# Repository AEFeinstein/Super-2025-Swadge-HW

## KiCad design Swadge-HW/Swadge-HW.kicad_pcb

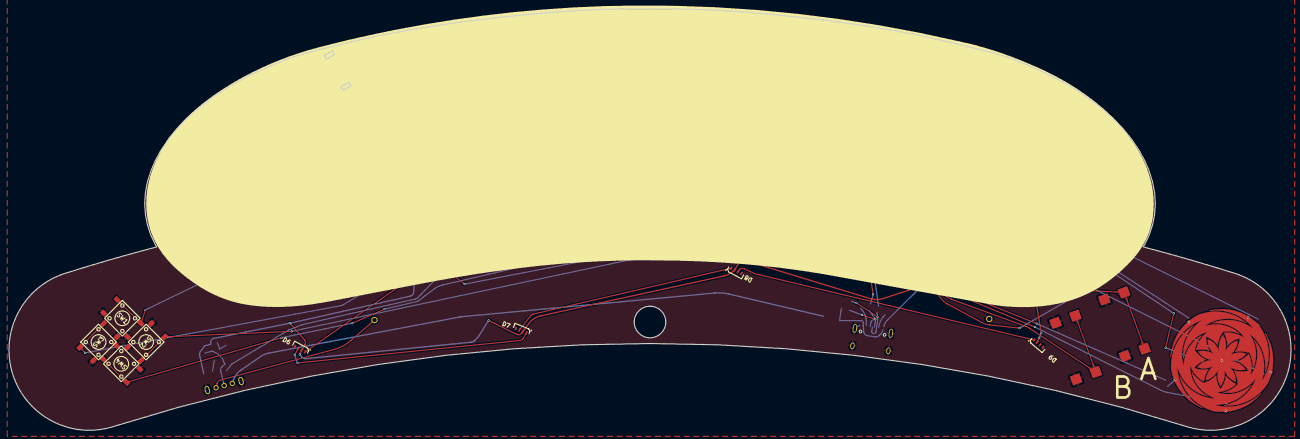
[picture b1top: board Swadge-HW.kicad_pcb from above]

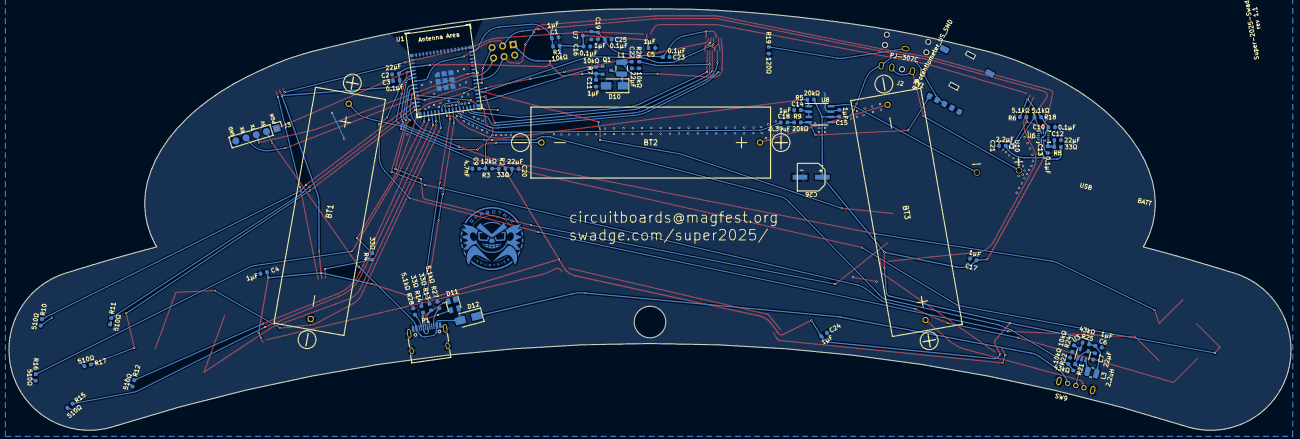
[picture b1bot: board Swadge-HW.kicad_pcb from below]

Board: 2 copper layers, 305.0 x 100.2 mm, 96 parts (71 on the bottom side), 76 nets.

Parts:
BT1, BT2, BT3: Battery; 2460
C1, C4, C5, C6, C11, C14, C15, C17, C19, C24: 1μF; C_0603_1608Metric
C2, C7, C12, C20, C22: 22μF; C_0603_1608Metric
C3, C10, C13, C16, C23, C25: 0.1μF; C_0603_1608Metric
C9: 4.7nF; C_0603_1608Metric
C18: 0.39uF; C_0603_1608Metric
C21: 2.2μF; C_0603_1608Metric
C26: 470μF; C_Radial_D6.3_L5.8_P5.34
D1, D2, D3, D4, D5, D6, D7, D8, D9: LC8812B-4020; 4020PAD
D10, D12: D; D_SMA
D11: SP0503BAHT; SOT-143
J1: SAO; PinSocket_2x03_P2.54mm_Vertical
J2: PJ-307C
J3: PGM; PinHeader_1x05_P2.54mm_Vertical
L1: 33uH_500mA; L_1210_3225Metric
L3: 2.2uH; L_1008_2520Metric
MK1: Microphone; INGHAi_MIC_GMI4013S-2C58DB
N1: Board Outline; longdog-outline
N2: Condiment Acrylic; longdog-condiment
P1: USB_C_Plug_USB2.0; USB_C_Receptacle_HRO_TYPE-C-31-M-12
Q1: Q_PMOS_GSD; SOT-23
R1, R7, R22, R24, R26: 10kΩ; R_0603_1608Metric
R2, R4, R8, R13, R14: 33Ω; R_0603_1608Metric
R3: 12kΩ; R_0603_1608Metric
R5, R9: 20kΩ; R_0603_1608Metric
R6, R18, R27, R28: 5.1kΩ; R_0603_1608Metric
R10, R11, R12, R15, R16, R17: 510Ω; R_0603_1608Metric
R19: 120Ω; R_0603_1608Metric
R21, R25: 43kΩ; R_0603_1608Metric
RV1: R_Potentiometer_US_SMD; RK10J11R001Y
SW1, SW2, SW3, SW4, SW5, SW6: YTS-D003-1A
SW7, SW8: B3FS-4002P; B3FS4002P
SW9: SW_SPDT_1825232-1; 1825232-1
U1: ESP32-S2-MINI-1
U2: RB017A1505A; NULL
U3: MT3410; SOT-23-5
U4: Touch_Teeth_5b
U5: RB017A1505A_Connector; HCTL HC-FPC-03-10-15RLTAG
U6: LSM6DSL; LGA-14_3x2.5mm_P0.5mm_LayoutBorder3x4y
U7: GENERIC_LDO_2.8; SOT-23
U8: FM8002A; SOP-8_3.9x4.9mm_P1.27mm
U9: INGHAi_GSPK2307P-8R1W; INGHAi GSPK2308P-8R0.5W
U10: BGA-4-.83x.83

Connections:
5VIN: D11.4 (K), D12.2 (A), J3.2, P1.A4_B9 (VBUS), P1.A9_B4 (VBUS)
+3V3: C2.1, C3.1, C4.1, C5.1, C6.1, C10.1, C11.1, C15.1, C16.1, C17.1, C21.1, C24.1, C26.1, D1.2 (VDD), D2.2 (VDD), D3.2 (VDD), D4.2 (VDD), D5.2 (VDD), D6.2 (VDD), D7.2 (VDD), D8.2 (VDD), D9.2 (VDD), J1.1, L3.1, Q1.2 (S), R1.1, R2.2, R5.1, R6.2, R7.1, R8.2, R18.1, R25.2, U1.3 (3V3), U6.5 (VDDIO), U6.12 (CS), U7.3 (IN), U8.6 (VDD), U10.B1 (VDD)
+5V: D12.1 (K), SW9.1 (A)
BATTMID: BT1.1 (+), BT2.2 (-)
BATTMID2: BT2.1 (+), BT3.2 (-)
BATTPLUS: BT3.1 (+), SW9.3 (C)
BTN_1: J3.1, SW1.1, SW1.2, U1.4 (GPIO0/BOOT)
BTN_2: SW2.1, SW2.2, U1.5 (GPIO1/ADC1_CH0)
BTN_3: SW3.1, SW3.2, U1.6 (GPIO2/ADC1_CH1)
BTN_4: SW4.1, SW4.2, U1.8 (GPIO4/ADC1_CH3)
BTN_5: SW5.1, SW5.2, U1.9 (GPIO5/ADC1_CH4)
BTN_6: SW6.1, SW6.2, U1.12 (GPIO8/ADC1_CH7)
BTN_7: SW7.1 (COM_1), SW7.2 (COM_2), U1.19 (GPIO15/ADC2_CH4/XTAL_32K_P)
BTN_8: SW8.1 (COM_1), SW8.2 (COM_2), U1.20 (GPIO16/ADC2_CH5/XTAL_32K_N)
CC1: P1.A5 (CC1), R28.2
CC2: P1.B5 (CC2), R27.2
EN: C1.1, R1.2, U1.45 (CHIP/PU/RESET)
GND: BT1.2 (-), C1.2, C2.2, C3.2, C4.2, C5.2, C6.2, C7.2, C9.1, C10.2, C11.2, C12.2, C13.2, C14.1, C15.2, C16.2, C17.2, C19.2, C20.2, C21.2, C22.2, C23.2, C24.2, C25.2, C26.2, D1.4 (GND), D2.4 (GND), D3.4 (GND), D4.4 (GND), D5.4 (GND), D6.4 (GND), D7.4 (GND), D8.4 (GND), D9.4 (GND), D10.2 (A), D11.1 (A), J1.2, J3.5, MK1.1 (-), P1.A1_B12 (GND), P1.A12_B1 (GND), P1.S1 (SHIELD), R19.1, R22.2, R24.1, R26.2, R27.1, R28.1, SW1.3, SW1.4, SW2.3, SW2.4, SW3.3, SW3.4, SW4.3, SW4.4, SW5.3, SW5.4, SW6.3, SW6.4, SW7.3 (NO_1), SW7.4 (NO_2), SW8.3 (NO_1), SW8.4 (NO_2), SW9.4 (D), SW9.5 (E), U1.1 (GND), U1.2 (GND), U1.30 (GND), U1.42 (GND), U1.43 (GND), U1.46 (GND), U1.47 (GND), U1.48 (GND), U1.49 (GND), U1.50 (GND), U1.51 (GND), U1.52 (GND), U1.53 (GND), U1.54 (GND), U1.55 (GND), U1.56 (GND), U1.57 (GND), U1.58 (GND), U1.59 (GND), U1.60 (GND), U1.61 (GND), U1.62 (GND), U1.63 (GND), U1.64 (GND), U1.65 (GND), U3.2 (GND), U5.1 (GND), U5.6 (GND), U5.9 (GND), U5.12 (LED-), U5.13 (LED-), U5.16 (GND), U5.17 (GND), U6.1 (SA0), U6.2 (SDx), U6.3 (SCx), U6.6 (GND), U6.7 (GND), U7.1 (GND), U8.7 (GND), U10.A1 (VSS)
GPIO40: J1.5, U1.36 (MTDO/JTAG/GPIO40)
GPIO42: J1.6, U1.38 (MTMS/JTAG/GPIO42)
LCD28: C19.1, C23.1, C25.1, U5.2 (VCC1.8V), U5.10 (VDD2.8V), U7.2 (OUT)
LED: R4.2, U1.35 (MTCK/JTAG/GPIO39)
MIC: C9.2, MK1.2 (+), R3.2, U1.11 (GPIO7/ADC1_CH6)
unnamed: C18.1, R9.1
unnamed: C20.1, R2.1, R3.1
unnamed: D1.1 (IN), R4.1
unnamed: D1.3 (OUT), D2.1 (IN)
unnamed: D2.3 (OUT), D3.1 (IN)
unnamed: D3.3 (OUT), D4.1 (IN)
unnamed: D4.3 (OUT), D5.1 (IN)
unnamed: D5.3 (OUT), D6.1 (IN)
unnamed: D6.3 (OUT), D7.1 (IN)
unnamed: D7.3 (OUT), D8.1 (IN)
unnamed: D8.3 (OUT), D9.1 (IN)
unnamed: D10.1 (K), L1.1, Q1.3 (D)
unnamed: J2.1, R19.2
unnamed: D11.2 (K), P1.A7 (DN1), P1.B7 (DN2), R14.2
unnamed: D11.3 (K), P1.A6 (DP1), P1.B6 (DP2), R13.2
unnamed: R24.2, R25.1, U3.5 (FB)
unnamed: L3.2, U3.3 (LX)
unnamed: R10.2, U4.1 (Bottom)
unnamed: R17.2, U4.6 (Center)
unnamed: R16.2, U4.5 (Left)
unnamed: R11.2, U4.2 (Right)
unnamed: R15.2, U4.4 (Top_Left)
unnamed: R12.2, U4.3 (Top_Right)
unnamed: C12.1, C13.1, R8.1, U6.8 (VDD)
unnamed: C14.2, U8.2 (Bypass), U8.3 (IN+)
unnamed: R9.2, RV1.1, U8.4 (IN-)
unnamed: J2.2, J2.5, RV1.2, U8.5 (VO1)
unnamed: U8.8 (VO2), U9.2 (-)
unnamed: J2.3, J2.4, U9.1 (+)
RX: J3.4, U1.40 (GPIO44/U0RXD/PROG)
SCL: J1.4, R6.1, U1.37 (MTDI/JTAG/GPIO41), U6.13 (SCL), U10.A2 (SCL)
SDA: J1.3, R18.2, U1.7 (GPIO3/ADC1_CH2), U6.14 (SDA), U10.B2 (SDA)
SNODE: C7.1, R21.2, SW9.2 (B), U3.1 (EN), U3.4 (VIN)
SPK: C18.2, U1.21 (ADC2_CH7/DAC_2/GPIO17)
SPK_SHDN: R5.2, U1.22 (ADC2_CH6/DAC_1/GPIO18), U8.1 (Shutdown)
TFTATP: Q1.1 (G), R7.2, U1.31 (GPIO35)
TFT_CS: U1.29 (GPIO34), U5.3 (CS)
TFT_FMARK: U1.28 (GPIO33), U5.11 (FMARK)
TFT_LEDA: C22.1, L1.2, U5.14 (LED+), U5.15 (LED+)
TFT_RESET: U1.34 (GPIO38), U5.4 (RESET)
TFT_RS: R26.1, U1.25 (GPIO21), U5.5 (RS)
TFT_SCL: U1.32 (GPIO36), U5.7 (SCL)
TFT_SDA: U1.33 (GPIO37), U5.8 (SDA)
TOUCH_1: R10.1, U1.13 (GPIO9/ADC1_CH8)
TOUCH_2: R11.1, U1.14 (GPIO10/ADC1_CH9)
TOUCH_3: R17.1, U1.15 (GPIO11/ADC2_CH0)
TOUCH_4: R16.1, U1.16 (GPIO12/ADC2_CH1)
TOUCH_5: R12.1, U1.17 (GPIO13/ADC2_CH2)
TOUCH_6: R15.1, U1.18 (GPIO14/ADC2_CH3)
TX: J3.3, U1.39 (GPIO43/U0TXD/PROG)
USB_D+: R13.1, U1.24 (USB_D+/ADC2_CH9/GPIO20)
USB_D-: R14.1, U1.23 (USB_D-/ADC2_CH8/GPIO19)
VMON: R21.1, R22.1, U1.10 (GPIO6/ADC1_CH5)

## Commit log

2024-10-06 Add longdog footprint
    longdog
2024-11-15 longdog
    new outline and silk for longdog variant
2024-11-15 longdog
    longdog layout
2024-11-15 art adjustment
2024-11-18 shape and routing
2024-11-20 generated mfg files for quoting
2024-11-29 Mfg data
2024-12-16 longdog 1.1
    edit BGA traces for manufacturability
2025-01-13 fix ground issue
    connected ground planes for D4 and power circuit
2025-01-13 mfg files
    gerber data upload
2025-01-14 * Add Vias * Increase size of power rails
2025-01-29 Update with charles's understanding of ground loops - there's still possibly a power fuzz issue but I am curious how it turns out.
